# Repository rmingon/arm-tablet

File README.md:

# ARM TABLET project with 480x800 screen connected with FSMC bus

## OLD VERSION VIDEO -> [VIDEO](https://www.youtube.com/shorts/6iCVGylVFGs)

### this tablet work with 10Ah lipo battery and STM32F407 mcu

## NEW VERSION BASED ON KICAD

### 3D

### PCB

### schematic

---

## OLD VERSION BASED ON FUSION360

### PCB

### schematic

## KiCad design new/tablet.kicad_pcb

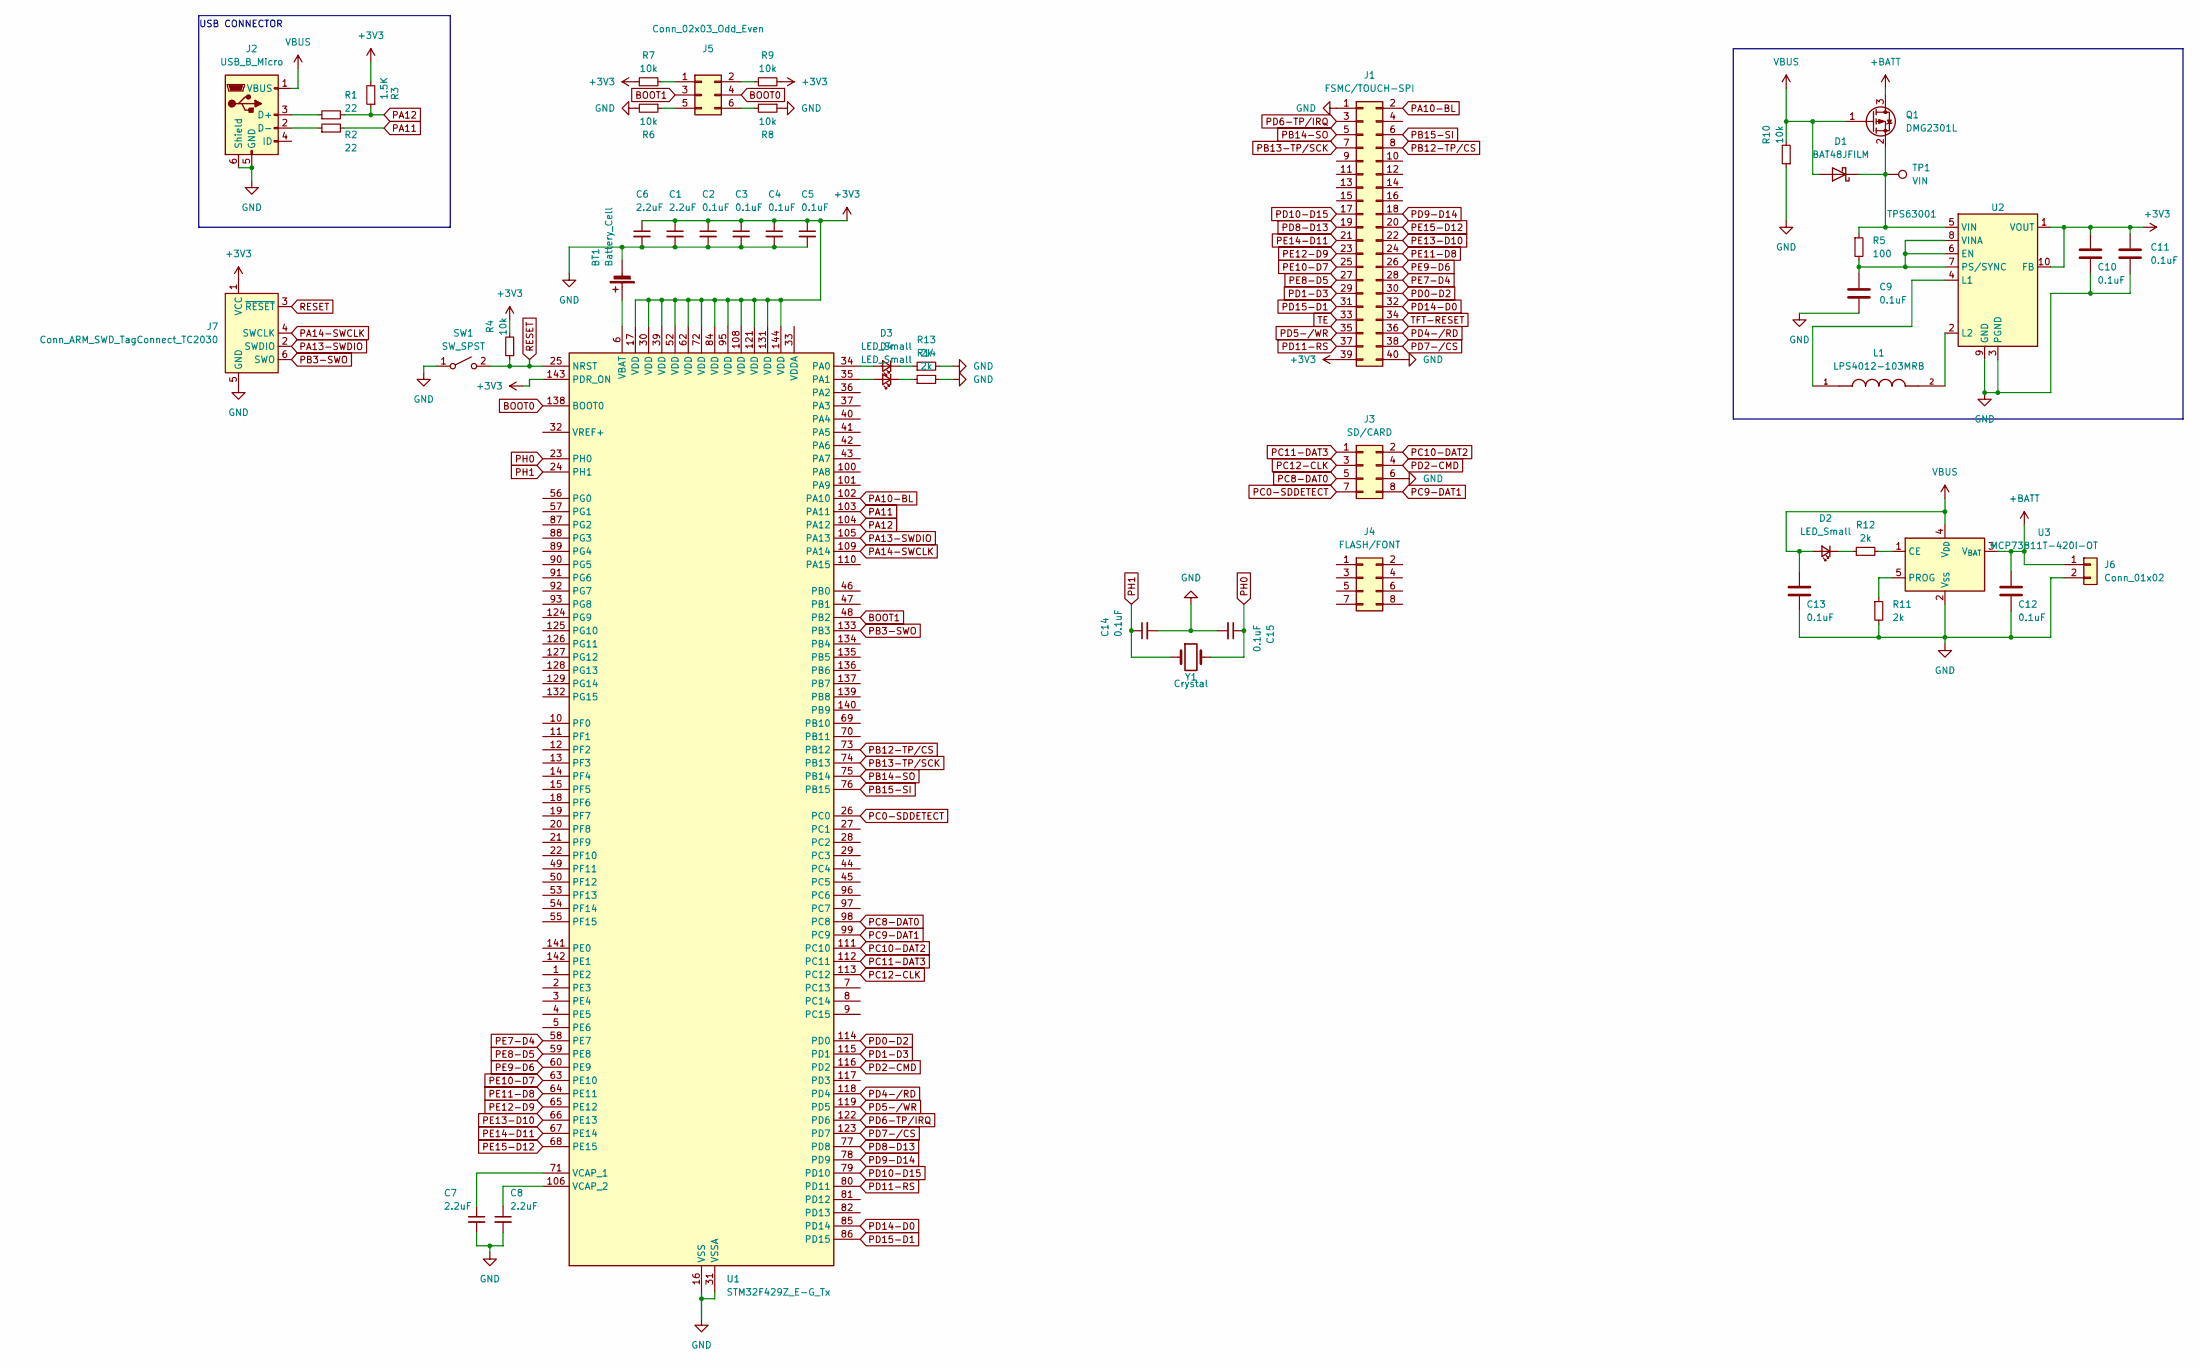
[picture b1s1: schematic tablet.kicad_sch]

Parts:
BT1: Battery_Cell; BatteryHolder_Keystone_3000_1x12mm
C1, C6, C7, C8: 2.2uF; C_0603_1608Metric
C2, C3, C4, C5, C9, C10, C11, C12, C13, C14, C15: 0.1uF; C_0603_1608Metric
D1: BAT48JFILM; D_SOD-323
D2, D3, D4: LED_Small; R_0603_1608Metric
J1: FSMC/TOUCH-SPI; PinHeader_2x20_P2.54mm_Vertical
J2: USB_B_Micro; USB_Micro-B_Molex-105017-0001
J3: SD/CARD; PinHeader_2x04_P2.54mm_Vertical
J4: FLASH/FONT; PinHeader_2x04_P2.54mm_Vertical
J5: Conn_02x03_Odd_Even; PinHeader_2x03_P2.54mm_Vertical_SMD
J6: Conn_01x02; PinSocket_1x02_P2.54mm_Vertical
J7: Conn_ARM_SWD_TagConnect_TC2030; PinHeader_1x06_P2.54mm_Vertical
L1: LPS4012-103MRB; L_Sunlord_SWPA4012S; PARTREV 08/01/13
Q1: DMG2301L; SOT-23
R1, R2: 22; R_0603_1608Metric
R3: 1.5K; R_0603_1608Metric
R4, R6, R7, R8, R9, R10: 10k; R_0603_1608Metric
R5: 100; R_0603_1608Metric
R11, R12, R13, R14: 2k; R_0603_1608Metric
SW1: SW_SPST; SW_SPST_CK_RS282G05A3
TP1: VIN; SolderWirePad_1x01_SMD_1x2mm
U1: STM32F429Z_E-G_Tx; LQFP-144_20x20mm_P0.5mm
U2: TPS63001; Texas_DRC0010J_ThermalVias
U3: MCP73811T-420I-OT; SOT-23-5
Y1: Crystal; Crystal_SMD_HC49-SD

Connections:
+3V3: C1.1, C2.1, C3.1, C4.1, C5.1, C6.1, C10.1, C11.1, J1.39, J7.1 (VCC), R3.2, R4.2, R7.1, R9.2, U1.17 (VDD), U1.30 (VDD), U1.39 (VDD), U1.52 (VDD), U1.62 (VDD), U1.72 (VDD), U1.84 (VDD), U1.95 (VDD), U1.108 (VDD), U1.121 (VDD), U1.131 (VDD), U1.143 (PDR_ON), U1.144 (VDD), U2.1 (VOUT), U2.10 (FB)
+BATT: C12.1, J6.1, Q1.3 (D), U3.3 (V_{BAT})
BOOT0: J5.4, U1.138 (BOOT0)
BOOT1: J5.3, U1.48 (PB2)
GND: BT1.2 (-), C1.2, C2.2, C3.2, C4.2, C5.2, C6.2, C7.2, C8.2, C9.2, C10.2, C11.2, C12.2, C13.2, C14.2, C15.2, J1.1, J1.40, J2.5 (GND), J2.6 (Shield), J3.6, J6.2, J7.5 (GND), R6.2, R8.1, R10.1, R11.2, R13.2, R14.2, SW1.1 (A), U1.16 (VSS), U1.31 (VSSA), U1.38 (VSS), U1.51 (VSS), U1.61 (VSS), U1.83 (VSS), U1.94 (VSS), U1.107 (VSS), U1.120 (VSS), U1.130 (VSS), U2.3 (PGND), U2.9 (GND), U2.11 (PGND), U3.2 (V_{SS})
unnamed: BT1.1 (+), U1.6 (VBAT)
unnamed: D1.1 (K), Q1.2 (S), R5.1, TP1.1, U2.5 (VIN)
unnamed: D2.1 (K), R12.1
unnamed: D3.2 (A), U1.34 (PA0)
unnamed: D3.1 (K), R13.1
unnamed: D4.2 (A), U1.35 (PA1)
unnamed: D4.1 (K), R14.1
unnamed: J2.3 (D+), R1.1
unnamed: J2.2 (D-), R2.1
unnamed: J5.1, R7.2
unnamed: J5.2, R9.1
unnamed: J5.5, R6.1
unnamed: J5.6, R8.2
unnamed: C7.1, U1.71 (VCAP_1)
unnamed: C8.1, U1.106 (VCAP_2)
unnamed: C9.1, R5.2, U2.6 (EN), U2.7 (PS/SYNC), U2.8 (VINA)
unnamed: L1.1, U2.4 (L1)
unnamed: L1.2, U2.2 (L2)
unnamed: R12.2, U3.1 (CE)
unnamed: R11.1, U3.5 (PROG)
PA10-BL: J1.2, U1.102 (PA10)
PA11: R2.2, U1.103 (PA11)
PA12: R1.2, R3.1, U1.104 (PA12)
PA13-SWDIO: J7.2 (SWDIO), U1.105 (PA13)
PA14-SWCLK: J7.4 (SWCLK), U1.109 (PA14)
PB3-SWO: J7.6 (SWO), U1.133 (PB3)
PB12-TP/CS: J1.8, U1.73 (PB12)
PB13-TP/SCK: J1.7, U1.74 (PB13)
PB14-SO: J1.5, U1.75 (PB14)
PB15-SI: J1.6, U1.76 (PB15)
PC0-SDDETECT: J3.7, U1.26 (PC0)
PC8-DAT0: J3.5, U1.98 (PC8)
PC9-DAT1: J3.8, U1.99 (PC9)
PC10-DAT2: J3.2, U1.111 (PC10)
PC11-DAT3: J3.1, U1.112 (PC11)
PC12-CLK: J3.3, U1.113 (PC12)
PD0-D2: J1.30, U1.114 (PD0)
PD1-D3: J1.29, U1.115 (PD1)
PD2-CMD: J3.4, U1.116 (PD2)
PD4-/RD: J1.36, U1.118 (PD4)
PD5-/WR: J1.35, U1.119 (PD5)
PD6-TP/IRQ: J1.3, U1.122 (PD6)
PD7-/CS: J1.38, U1.123 (PD7)
PD8-D13: J1.19, U1.77 (PD8)
PD9-D14: J1.18, U1.78 (PD9)
PD10-D15: J1.17, U1.79 (PD10)
PD11-RS: J1.37, U1.80 (PD11)
PD14-D0: J1.32, U1.85 (PD14)
PD15-D1: J1.31, U1.86 (PD15)
PE7-D4: J1.28, U1.58 (PE7)
PE8-D5: J1.27, U1.59 (PE8)
PE9-D6: J1.26, U1.60 (PE9)
PE10-D7: J1.25, U1.63 (PE10)
PE11-D8: J1.24, U1.64 (PE11)
PE12-D9: J1.23, U1.65 (PE12)
PE13-D10: J1.22, U1.66 (PE13)
PE14-D11: J1.21, U1.67 (PE14)
PE15-D12: J1.20, U1.68 (PE15)
PH0: C15.1, U1.23 (PH0), Y1.2
PH1: C14.1, U1.24 (PH1), Y1.1
RESET: J7.3 (~RESET), R4.1, SW1.2 (B), U1.25 (NRST)
TE: J1.33
TFT-RESET: J1.34
VBUS: C13.1, D1.2 (A), D2.2 (A), J2.1 (VBUS), Q1.1 (G), R10.2, U3.4 (V_{DD})

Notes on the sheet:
USB CONNECTOR

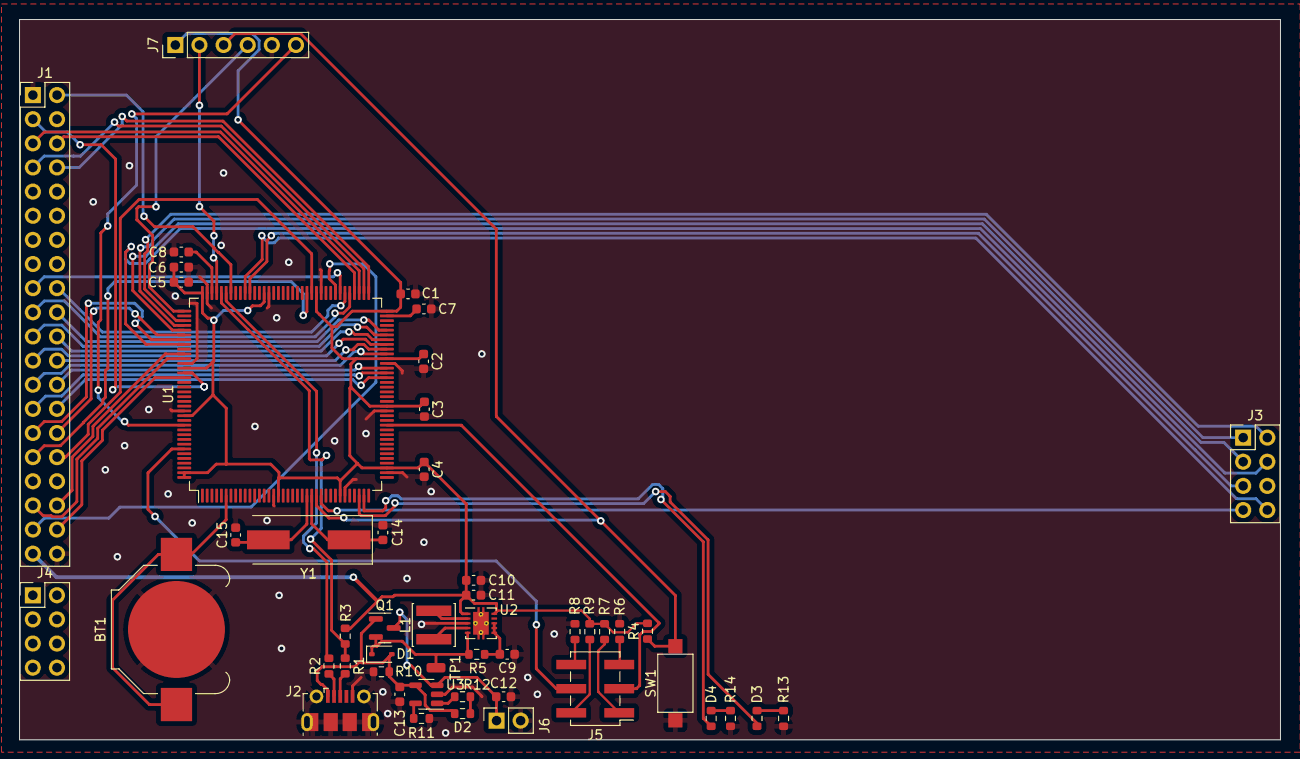
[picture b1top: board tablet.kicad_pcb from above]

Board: 2 copper layers, 132.7 x 75.8 mm, 49 parts (0 on the bottom side), 67 nets.

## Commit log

2023-09-29 add readme
2023-10-01 pcb view
2023-10-01 schematic view
2023-10-01 add view in readme
2023-10-04 add fusion file
2023-10-04 set fusion360 old
2023-10-04 first commit kicad
2023-10-04 add stm32f429 + screen connector
2023-10-04 add usb connector
2023-10-04 add components
2023-10-04 add footprints
2023-10-04 update project
2023-10-04 screen datasheet
2023-10-04 place header on pcb
2023-10-04 wiring screen + sdcard
2023-10-04 add video
2023-10-04 add new version text
2023-10-04 add kicad file
2023-10-04 add TPS63001
2023-10-04 add wiring + battery charging
2023-10-04 new view
2023-10-04 wiring
2023-10-04 add led
2023-10-04 update readme view
2023-10-04 send for production
2023-10-04 update view link
2023-10-05 move video link
